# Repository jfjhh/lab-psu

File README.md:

# Lab Power Supply

This repository contains the KiCAD files and documentation for a simple lab
power supply.

The KiCAD files are in the top level.

The exported gerber and NC drill files are in the `gerbers` directory.

The documentation for the project is in the `doc` directory. This includes:

- KiCAD and DigiKey bills of materials in `doc/bom`.
- Datasheets for all ICs used in `doc/datasheets`.
- PCB layer PDFs in `doc/pcb`.
- A schematic PDF at `doc/psu-schematic.pdf`.
- A comprehensive manual in `doc/manual`.

Note that some parts on hand were used and not included in the DigiKey BOM.
These discrepancies are documented in `doc/bom/non-digikey.txt`.

*The development of this power supply was generously funded by the Reed College
Physics Department during the summer of 2019.*

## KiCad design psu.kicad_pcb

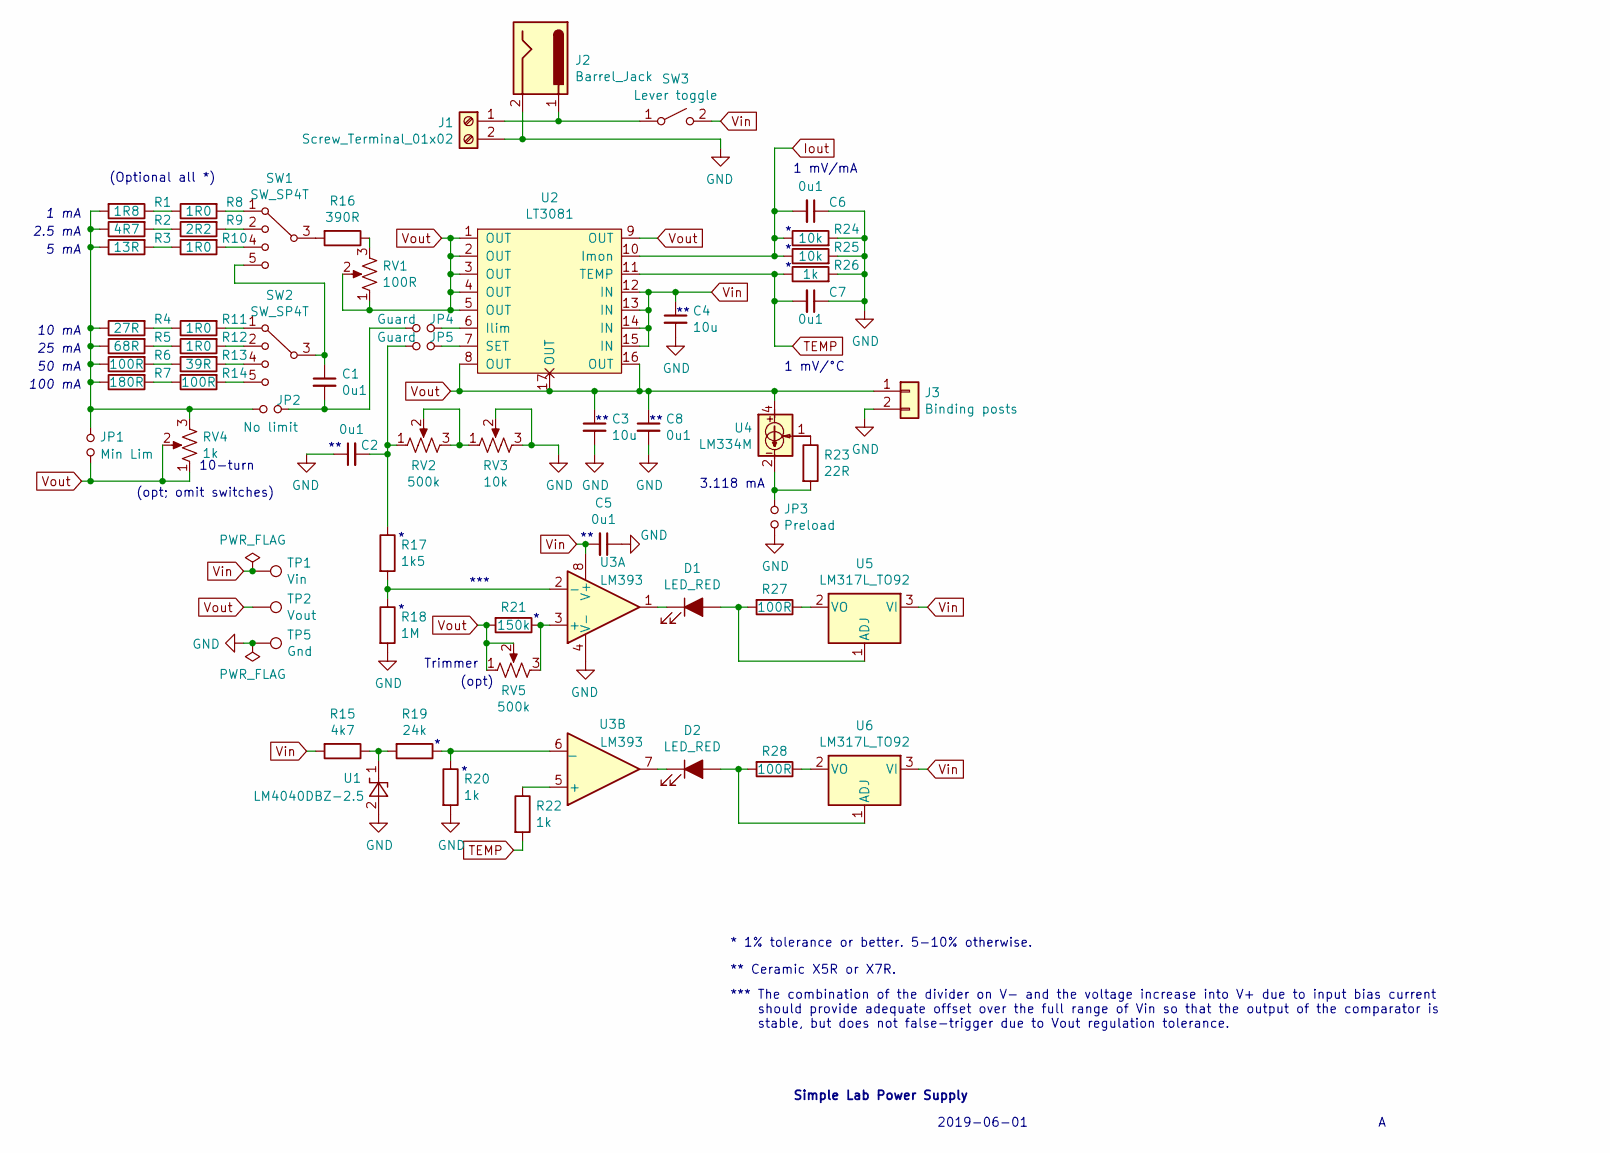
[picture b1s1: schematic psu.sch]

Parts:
C1, C2, C5, C6, C7, C8: 0u1; C_Disc_D5.0mm_W2.5mm_P2.50mm
C3, C4: 10u; C_1206_3216Metric_Pad1.42x1.75mm_HandSolder
D1, D2: LED_RED; LED_D3.0mm
J1: Screw_Terminal_01x02; TerminalBlock_MetzConnect_Type094_RT03502HBLU_1x02_P5.00mm_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
J2: Barrel_Jack; BarrelJack_Horizontal
J3: Binding posts; Binding Posts
JP1: Min Lim; PinHeader_1x02_P2.54mm_Vertical
JP2: No limit; PinHeader_1x02_P2.54mm_Vertical
JP3: Preload; PinHeader_1x02_P2.54mm_Vertical
JP4, JP5: Guard; Guard_Jumper
R1: 1R8; R_1206_3216Metric_Pad1.42x1.75mm_HandSolder
R2: 4R7; R_1206_3216Metric_Pad1.42x1.75mm_HandSolder
R3: 13R; R_1206_3216Metric_Pad1.42x1.75mm_HandSolder
R4: 27R; R_1206_3216Metric_Pad1.42x1.75mm_HandSolder
R5: 68R; R_1206_3216Metric_Pad1.42x1.75mm_HandSolder
R6, R14: 100R; R_1206_3216Metric_Pad1.42x1.75mm_HandSolder
R7: 180R; R_1206_3216Metric_Pad1.42x1.75mm_HandSolder
R8, R10, R11, R12: 1R0; R_1206_3216Metric_Pad1.42x1.75mm_HandSolder
R9: 2R2; R_1206_3216Metric_Pad1.42x1.75mm_HandSolder
R13: 39R; R_1206_3216Metric_Pad1.42x1.75mm_HandSolder
R15: 4k7; R_Axial_DIN0207_L6.3mm_D2.5mm_P10.16mm_Horizontal
R16: 390R; R_Axial_DIN0207_L6.3mm_D2.5mm_P10.16mm_Horizontal
R17: 1k5; R_1206_3216Metric_Pad1.42x1.75mm_HandSolder
R18: 1M; R_1206_3216Metric_Pad1.42x1.75mm_HandSolder
R19: 24k; R_1206_3216Metric_Pad1.42x1.75mm_HandSolder
R20, R26: 1k; R_1206_3216Metric_Pad1.42x1.75mm_HandSolder
R21: 150k; R_1206_3216Metric_Pad1.42x1.75mm_HandSolder
R22: 1k; R_Axial_DIN0207_L6.3mm_D2.5mm_P10.16mm_Horizontal
R23: 22R; R_Axial_DIN0207_L6.3mm_D2.5mm_P10.16mm_Horizontal
R24, R25: 10k; R_1206_3216Metric_Pad1.42x1.75mm_HandSolder
R27, R28: 100R; R_Axial_DIN0207_L6.3mm_D2.5mm_P10.16mm_Horizontal
RV1: 100R; Trim_pot_Bourns_TC33X-2-101E
RV2: 500k; Potentiometer_Piher_PC-16_Single_Horizontal
RV3: 10k; Potentiometer_Piher_PC-16_Single_Horizontal
RV4: 1k; Potentiometer_Piher_PC-16_Single_Horizontal
RV5: 500k; Trim_pot_Bourns_TC33X-2-101E
SW1, SW2: SW_SP4T; SP4T_CK_SK-14D01-G-6
SW3: Lever toggle; SW_SPST_Lever_Rubber
TP1: Vin; TestPoint_Bridge_Pitch2.54mm_Drill1.3mm
TP2: Vout; TestPoint_Bridge_Pitch2.54mm_Drill1.3mm
TP5: Gnd; TestPoint_Bridge_Pitch2.54mm_Drill1.3mm
U1: LM4040DBZ-2.5; SOT-23
U2: LT3081; HTSSOP-16-1EP_4.4x5mm_P0.65mm_EP3.4x5mm_Mask3x3mm_ThermalVi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
U3: LM393; SOIC-8_3.9x4.9mm_P1.27mm
U4: LM334M; SOIC-8_3.9x4.9mm_P1.27mm
U5, U6: LM317L_TO92; TO-92_Inline

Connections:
GND: C2.1, C3.2, C4.2, C5.1, C6.1, C7.1, C8.2, J1.2, J2.2, J3.2, JP3.2, R18.2, R20.2, R24.2, R25.2, R26.2, RV3.2, RV3.3, TP5.1, U1.2 (A), U3.4 (V-)
Iout: C6.2, R24.1, R25.1, U2.10 (Imon)
unnamed: C1.1, SW1.5, SW2.3
unnamed: C1.2, JP2.1, JP4.2
unnamed: C2.2, JP5.2, R17.1, RV2.1
unnamed: D1.1 (K), U3.1
unnamed: D1.2 (A), R27.2, U5.1 (ADJ)
unnamed: D2.1 (K), U3.7
unnamed: D2.2 (A), R28.2, U6.1 (ADJ)
unnamed: J1.1, J2.1, SW3.1 (A)
unnamed: JP1.1, JP2.2, R1.2, R2.1, R3.1, R4.1, R5.1, R6.1, R7.1, RV4.3
unnamed: JP3.1, R23.2, U4.2, U4.3, U4.6, U4.7
unnamed: JP4.1, U2.6 (Ilim)
unnamed: JP5.1, U2.7 (SET)
unnamed: R1.1, R8.1
unnamed: R2.2, R9.1
unnamed: R8.2, SW1.1
unnamed: R9.2, SW1.2
unnamed: R3.2, R10.1
unnamed: R10.2, SW1.4
unnamed: R4.2, R11.1
unnamed: R11.2, SW2.1
unnamed: R5.2, R12.1
unnamed: R12.2, SW2.2
unnamed: R6.2, R13.1
unnamed: R13.2, SW2.4
unnamed: R7.2, R14.1
unnamed: R14.2, SW2.5
unnamed: R15.1, R19.2, U1.1 (K)
unnamed: R16.1, RV1.3
unnamed: R16.2, SW1.3
unnamed: R17.2, R18.1, U3.2 (-)
unnamed: R19.1, R20.1, U3.6 (_)
unnamed: R21.1, RV5.3, U3.3 (+)
unnamed: R22.1, U3.5 (+)
unnamed: R23.1, U4.1
unnamed: R27.1, U5.2 (VO)
unnamed: R28.1, U6.2 (VO)
unnamed: RV2.2, RV2.3, RV3.1
TEMP: C7.2, R22.2, R26.1, U2.11 (TEMP)
Vin: C4.1, C5.2, R15.2, SW3.2 (B), TP1.1, U2.12 (IN), U2.13 (IN), U2.14 (IN), U2.15 (IN), U3.8 (V+), U5.3 (VI), U6.3 (VI)
Vout: C3.1, C8.1, J3.1, JP1.2, R21.2, RV1.1, RV1.2, RV4.1, RV4.2, RV5.1, RV5.2, TP2.1, U2.1 (OUT), U2.2 (OUT), U2.3 (OUT), U2.4 (OUT), U2.5 (OUT), U2.8 (OUT), U2.9 (OUT), U2.16 (OUT), U2.17 (OUT), U4.4

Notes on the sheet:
2019-06-01
Simple Lab Power Supply
1 mA
2.5 mA
5 mA
10 mA
25 mA
50 mA
100 mA
1 mV/°C
*** The combination of the divider on V- and the voltage increase into V+ due to input bias current should provide adequate offset over the full range of Vin so that the output of the comparator is stable, but does not false-trigger due to Vout regulation tolerance.
***
** Ceramic X5R or X7R.
* 1% tolerance or better. 5-10% otherwise.
3.118 mA
(Optional all *)
1 mV/mA
10-turn
(opt; omit switches)
Trimmer
(opt)

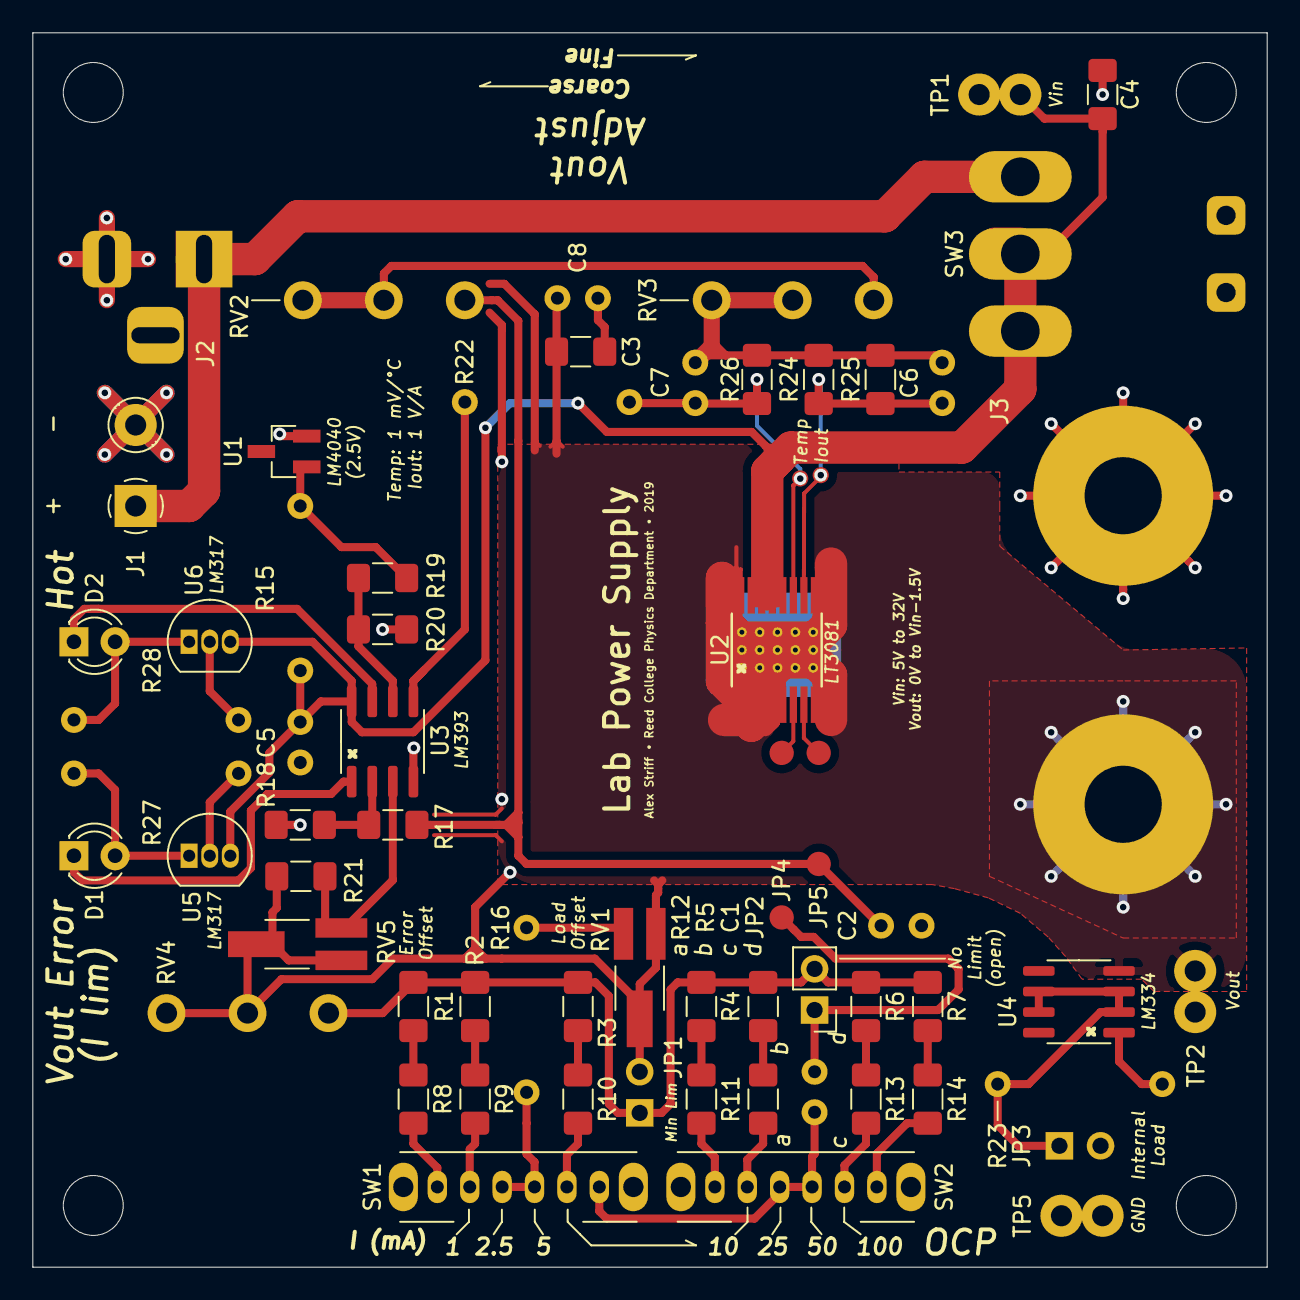
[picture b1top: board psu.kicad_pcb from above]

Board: 2 copper layers, 76.2 x 76.2 mm, 63 parts (0 on the bottom side), 42 nets.

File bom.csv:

Source:,C:\Users\opticslab\Documents\KiCad\lab-psu\psu.sch,,,,,
Date:,6/5/2019 15:52,,,,,
Tool:,Eeschema (5.1.2)-1,,,,,
Generator:,C:\Program Files\KiCad\bin\scripting\plugins/bom_csv_grouped_by_value.py,,,,,
Component Count:,48,,,,,
,,,,,,
Individual Components:,,,,,,
,,,,,,
Item,Qty,Reference(s),Value,LibPart,Footprint,Datasheet
,,C1,0u1,Device:C_Small,,~
,,C2,0u1,Device:C_Small,,~
,,C3,10u,Device:C_Small,,~
,,C4,0u1,Device:C_Small,,~
,,D1,LED_RED,Device:LED_ALT,,~
,,D2,LED_RED,Device:LED_ALT,,~
,,J1,Screw_Terminal_01x02,Connector:Screw_Terminal_01x02,,~
,,J2,Barrel_Jack,Connector:Barrel_Jack,,~
,,J3,Conn_01x02,Connector_Generic:Conn_01x02,,~
,,R1,1R8,Device:R,,~
,,R2,4R7,Device:R,,~
,,R3,13R,Device:R,,~
,,R4,27R,Device:R,,~
,,R5,68R,Device:R,,~
,2,R6,100R,Device:R,,~
,,R7,180R,Device:R,,~
,4,R8,1R0,Device:R,,~
,,R9,2R2,Device:R,,~
,X,R10,1R0,Device:R,,~
,X,R11,1R0,Device:R,,~
,X,R12,1R0,Device:R,,~
,,R13,39R,Device:R,,~
,X,R14,100R,Device:R,,~
,N,R15,4k7,Device:R,,~
,N,R16,390R,Device:R,,~
,,R17,1k5,Device:R,,~
,,R18,1M,Device:R,,~
,,R19,24k,Device:R,,~
,2,R20,1k,Device:R,,~
,,R21,150k,Device:R,,~
,N,R22,1k,Device:R,,~
,N,R23,22R,Device:R,,~
,,R24,5k,Device:R,,~
,X,R25,1k,Device:R,,~
,N,R26,470R,Device:R,,~
,N,R27,470R,Device:R,,~
,,RV1,100R,Device:R_POT,,~
,,RV2,500k,Device:R_POT_US,,~
,,RV3,10k,Device:R_POT_US,,~
,,SW1,SW_SP4T,psu-sch:SW_SP4T,,~
,,SW2,SW_SP4T,psu-sch:SW_SP4T,,~
,,SW3,SW_SPST,Switch:SW_SPST,,~
,,U1,LM4040DBZ-2.5,Reference_Voltage:LM4040DBZ-2.5,Package_TO_SOT_SMD:SOT-23,http://www.ti.com/lit/ds/symlink/lm4040-n.pdf
,,U2,LT3081,psu-sch:LT3081,,
,,U3,LM358,Amplifier_Operational:LM358,,http://www.ti.com/lit/ds/symlink/lm2904-n.pdf
,,U4,LM334M,Reference_Current:LM334M,Package_SO:SOIC-8_3.9x4.9mm_P1.27mm,http://www.ti.com/lit/ds/symlink/lm134.pdf
,,U5,LM317L_TO92,Regulator_Linear:LM317L_TO92,Package_TO_SOT_THT:TO-92_Inline,http://www.ti.com/lit/ds/snvs775k/snvs775k.pdf
,,U6,LM317L_TO92,Regulator_Linear:LM317L_TO92,Package_TO_SOT_THT:TO-92_Inline,http://www.ti.com/lit/ds/snvs775k/snvs775k.pdf
,,,,,,
,,,,,,
,,,,,,
Collated Components:,,,,,,
,,,,,,
Item,Qty,Reference(s),Value,LibPart,Footprint,Datasheet
1,3,"C1, C2, C4",0u1,Device:C_Small,,~
2,1,C3,10u,Device:C_Small,,~
3,2,"D1, D2",LED_RED,Device:LED_ALT,,~
4,1,J1,Screw_Terminal_01x02,Connector:Screw_Terminal_01x02,,~
5,1,J2,Barrel_Jack,Connector:Barrel_Jack,,~
6,1,J3,Conn_01x02,Connector_Generic:Conn_01x02,,~
7,1,R1,1R8,Device:R,,~
8,1,R2,4R7,Device:R,,~
9,1,R3,13R,Device:R,,~
10,1,R4,27R,Device:R,,~
11,1,R5,68R,Device:R,,~
12,2,"R6, R14",100R,Device:R,,~
13,1,R7,180R,Device:R,,~
14,4,"R8, R10, R11, R12",1R0,Device:R,,~
15,1,R9,2R2,Device:R,,~
16,1,R13,39R,Device:R,,~
17,1,R15,4k7,Device:R,,~
18,1,R16,390R,Device:R,,~
19,1,R17,1k5,Device:R,,~
20,1,R18,1M,Device:R,,~
21,1,R19,24k,Device:R,,~
22,3,"R20, R22, R25",1k,Device:R,,~
23,1,R21,150k,Device:R,,~
24,1,R23,22R,Device:R,,~
25,1,R24,5k,Device:R,,~
26,2,"R26, R27",470R,Device:R,,~
27,1,RV1,100R,Device:R_POT,,~
28,1,RV2,500k,Device:R_POT_US,,~
29,1,RV3,10k,Device:R_POT_US,,~
30,2,"SW1, SW2",SW_SP4T,psu-sch:SW_SP4T,,~
31,1,SW3,SW_SPST,Switch:SW_SPST,,~
32,1,U1,LM4040DBZ-2.5,Reference_Voltage:LM4040DBZ-2.5,Package_TO_SOT_SMD:SOT-23,http://www.ti.com/lit/ds/symlink/lm4040-n.pdf
33,1,U2,LT3081,psu-sch:LT3081,,
34,1,U3,LM358,Amplifier_Operational:LM358,,http://www.ti.com/lit/ds/symlink/lm2904-n.pdf
35,1,U4,LM334M,Reference_Current:LM334M,Package_SO:SOIC-8_3.9x4.9mm_P1.27mm,http://www.ti.com/lit/ds/symlink/lm134.pdf
36,2,"U5, U6",LM317L_TO92,Regulator_Linear:LM317L_TO92,Package_TO_SOT_THT:TO-92_Inline,http://www.ti.com/lit/ds/snvs775k/snvs775k.pdf

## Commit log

2019-05-31 New project
2019-06-04 Start Rev A
    The LT3081 does it all.
2019-06-04 Closer to final; need offset
    Need to deal with input offset for current protection / regulation comparator. Add an adder before the comparator?
2019-06-04 Fix PDF
2019-06-05 Rev A schematic finished!
    May need to slightly tweak resistor values based on available stock.
2019-06-05 Finalization of resistor values
2019-06-06 Most footprints entered
2019-06-06 Finished footprints
    Also decided to use a comparator instead of the LM358 (would not handle inputs above Vin).
2019-06-07 Started routing
2019-06-07 Minor schematic tweaks; more routing
2019-06-07 Mostly routed
2019-06-08 More routing; some issues
2019-06-09 It's all connected man
2019-06-09 Tweaks
2019-06-10 Silkscreen overhaul
2019-06-11 More silkscreen
2019-06-11 Fixed some 90 degree track-plane junctions
2019-06-11 Cleaned up silkscreen
2019-06-12 Final changes before manufacture
2019-06-12 Minor tweak to Vout fill; add gerbers
2019-06-12 Add PCB and datasheet PDFs
2019-06-12 Added BOMs, a README, and started the manual
2019-06-13 Added to manual: motivation and usage
2019-06-13 Add manual colophon
2019-06-14 Ignore generated TeX files in manual
2019-06-14 Added schematic, PCB layers, and BOM to manual
2019-06-14 Manual: some principles of operation
2019-06-14 Add 2up and 2up-abridged versions of datasheets
2019-06-15 Started to explain offset circuit
2019-06-15 Finished operating principles; added gnuplots
2019-07-08 Rev B
